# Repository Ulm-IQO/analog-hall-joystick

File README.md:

# Adjustable, Analog Hall Joystick

This joystick was designed to replace the failing resisitve joystick of a 
PI Micos SMC Corvus eco three-axis stepper motor controller.

The design has a primary XYZ joystick (Apem HF46S10) where the Z axis is 
the rotatable shaft and a secondary stick (Apem BF150A01BK0500) only 
for the Z axis.

Which Z axis is applied at the analog output can be controlled with a switch
while all four signals are available at the analog inputs of the integrated
Teensy 3.x microcontroller board.

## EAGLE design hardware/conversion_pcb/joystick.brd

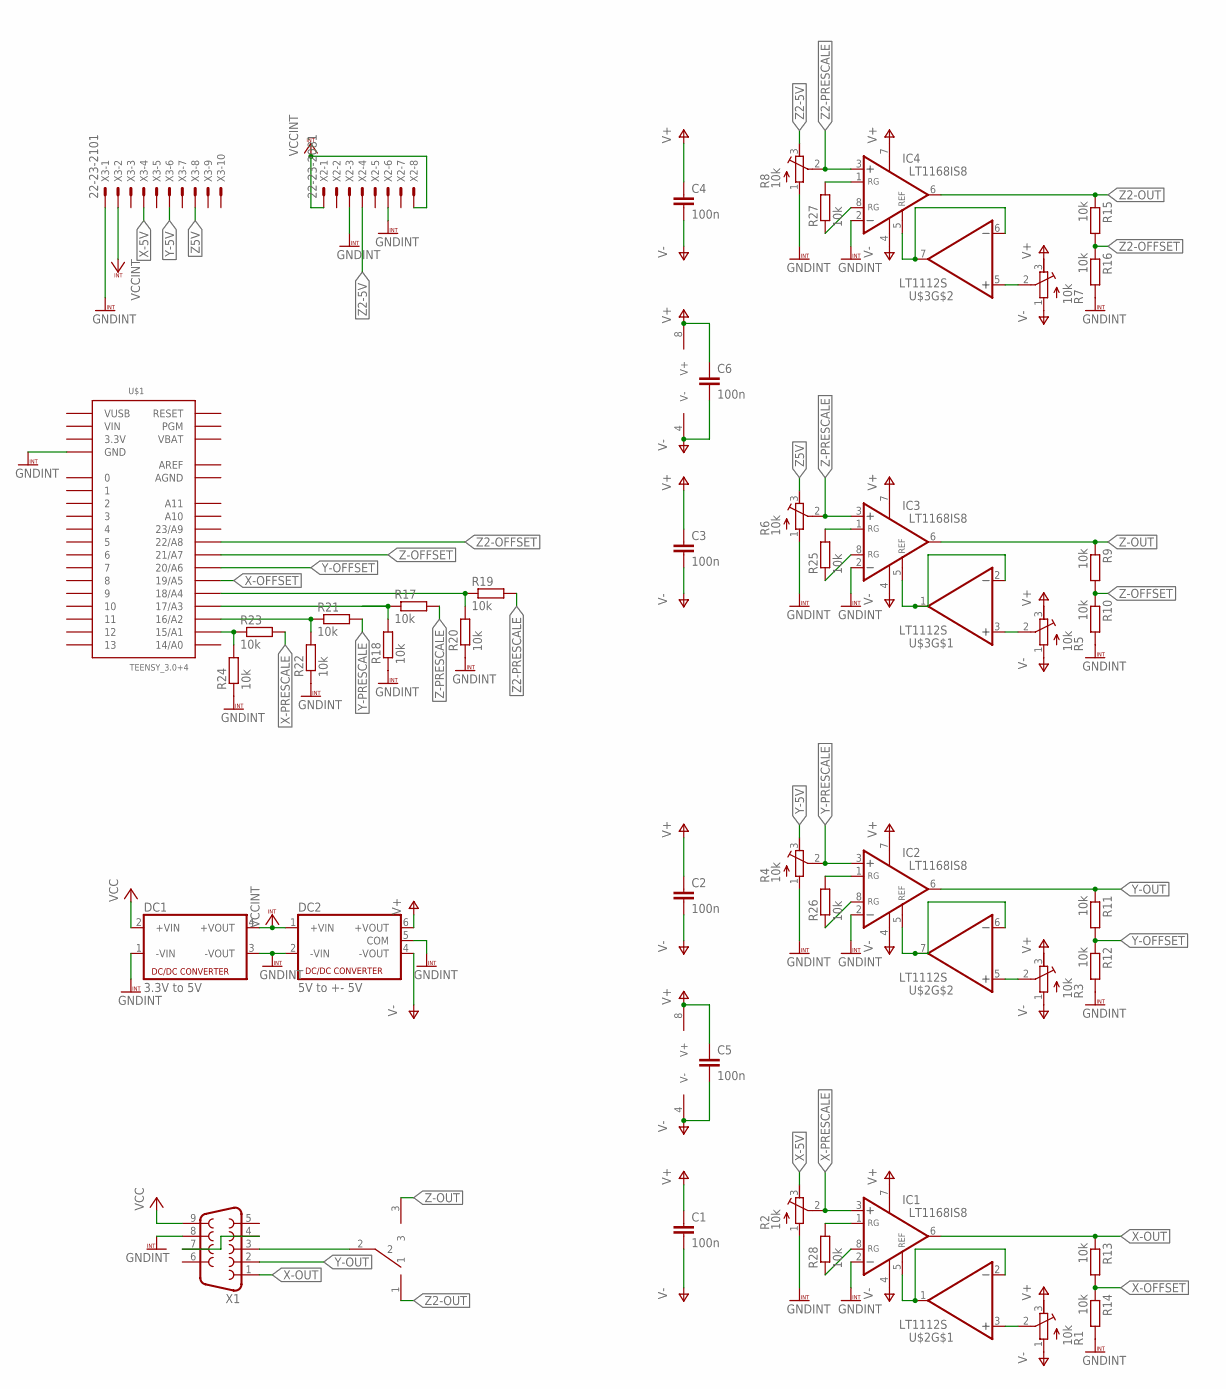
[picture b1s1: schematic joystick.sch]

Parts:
C1, C2, C3, C4, C5, C6: 100n; C1206
DC1: 3.3V to 5V; NME
DC2: 5V to +- 5V; NMA
IC1, IC2, IC3, IC4: LT1168IS8; SOIC8
R1, R2, R3, R4, R5, R6, R7, R8: 10k; RTRIM64W
R9, R10, R11, R12, R13, R14, R15, R16, R17, R18, R19, R20, R21, R22, R23, R24, R25, R26, R27, R28: 10k; R1206
U$1: TEENSY_3.0+4
U$2, U$3: LT1112S; SOIC8
U$4: MS12ASG40
X1: F09HP
X2: 22-23-2081
X3: 22-23-2101

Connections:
3.3V: U$1.3.3V, U$1.3.3V1 (3.3V)
AGND: U$1.AGND
AREF: U$1.AREF
GNDINT: DC1.1 (-VIN), DC1.3 (-VOUT), DC2.2 (-VIN), DC2.5 (COM), IC1.2 (-IN), IC2.2 (-IN), IC3.2 (-IN), IC4.2 (-IN), R2.1 (A), R4.1 (A), R6.1 (A), R8.1 (A), R10.2, R12.2, R14.2, R16.2, R18.1, R20.1, R22.1, R24.1, U$1.GND, U$1.GND1 (GND), X1.8, X2.3, X2.6, X3.1
unnamed: R1.2 (S), U$2.3 (+IN)
unnamed: R3.2 (S), U$2.5 (+IN)
unnamed: R5.2 (S), U$3.3 (+IN)
unnamed: R7.2 (S), U$3.5 (+IN)
unnamed: IC1.5 (REF), U$2.1 (OUT), U$2.2 (-IN)
unnamed: IC2.5 (REF), U$2.6 (-IN), U$2.7 (OUT)
unnamed: IC3.5 (REF), U$3.1 (OUT), U$3.2 (-IN)
unnamed: IC4.5 (REF), U$3.6 (-IN), U$3.7 (OUT)
unnamed: X1.4, X1.7
unnamed: U$4.2, X1.3
unnamed: R17.1, R18.2, U$1.17/A3
unnamed: R19.1, R20.2, U$1.18/A4
unnamed: R21.1, R22.2, U$1.16/A2
unnamed: R23.1, R24.2, U$1.15/A1
unnamed: IC1.8 (RG), R28.1
unnamed: IC1.1 (RG), R28.2
unnamed: IC2.1 (RG), R26.2
unnamed: IC2.8 (RG), R26.1
unnamed: IC3.1 (RG), R25.2
unnamed: IC3.8 (RG), R25.1
unnamed: IC4.8 (RG), R27.1
unnamed: IC4.1 (RG), R27.2
V+: C1.1, C2.1, C3.1, C4.1, C5.1, C6.1, DC2.6 (+VOUT), IC1.7 (V+), IC2.7 (V+), IC3.7 (V+), IC4.7 (V+), R1.3 (E), R3.3 (E), R5.3 (E), R7.3 (E), U$2.8 (V+), U$3.8 (V+)
V-: C1.2, C2.2, C3.2, C4.2, C5.2, C6.2, DC2.4 (-VOUT), IC1.4 (V-), IC2.4 (V-), IC3.4 (V-), IC4.4 (V-), R1.1 (A), R3.1 (A), R5.1 (A), R7.1 (A), U$2.4 (V-), U$3.4 (V-)
VBAT: U$1.VBAT
VCC: DC1.2 (+VIN), X1.9
VCCINT: DC1.4 (+VOUT), DC2.1 (+VIN), X2.1, X2.8, X3.2
VIN: U$1.VIN
VUSB: U$1.VUSB
X-5V: R2.3 (E), X3.4
X-OFFSET: R13.2, R14.1, U$1.19/A5
X-OUT: IC1.6 (OUT), R13.1, X1.1
X-PRESCALE: IC1.3 (+IN), R2.2 (S), R23.2
Y-5V: R4.3 (E), X3.6
Y-OFFSET: R11.2, R12.1, U$1.20/A6
Y-OUT: IC2.6 (OUT), R11.1, X1.2
Y-PRESCALE: IC2.3 (+IN), R4.2 (S), R21.2
Z2-5V: R8.3 (E), X2.4
Z2-OFFSET: R15.2, R16.1, U$1.22/A8
Z2-OUT: IC4.6 (OUT), R15.1, U$4.1
Z2-PRESCALE: IC4.3 (+IN), R8.2 (S), R19.2
Z5V: R6.3 (E), X3.8
Z-OFFSET: R9.2, R10.1, U$1.21/A7
Z-OUT: IC3.6 (OUT), R9.1, U$4.3
Z-PRESCALE: IC3.3 (+IN), R6.2 (S), R17.2

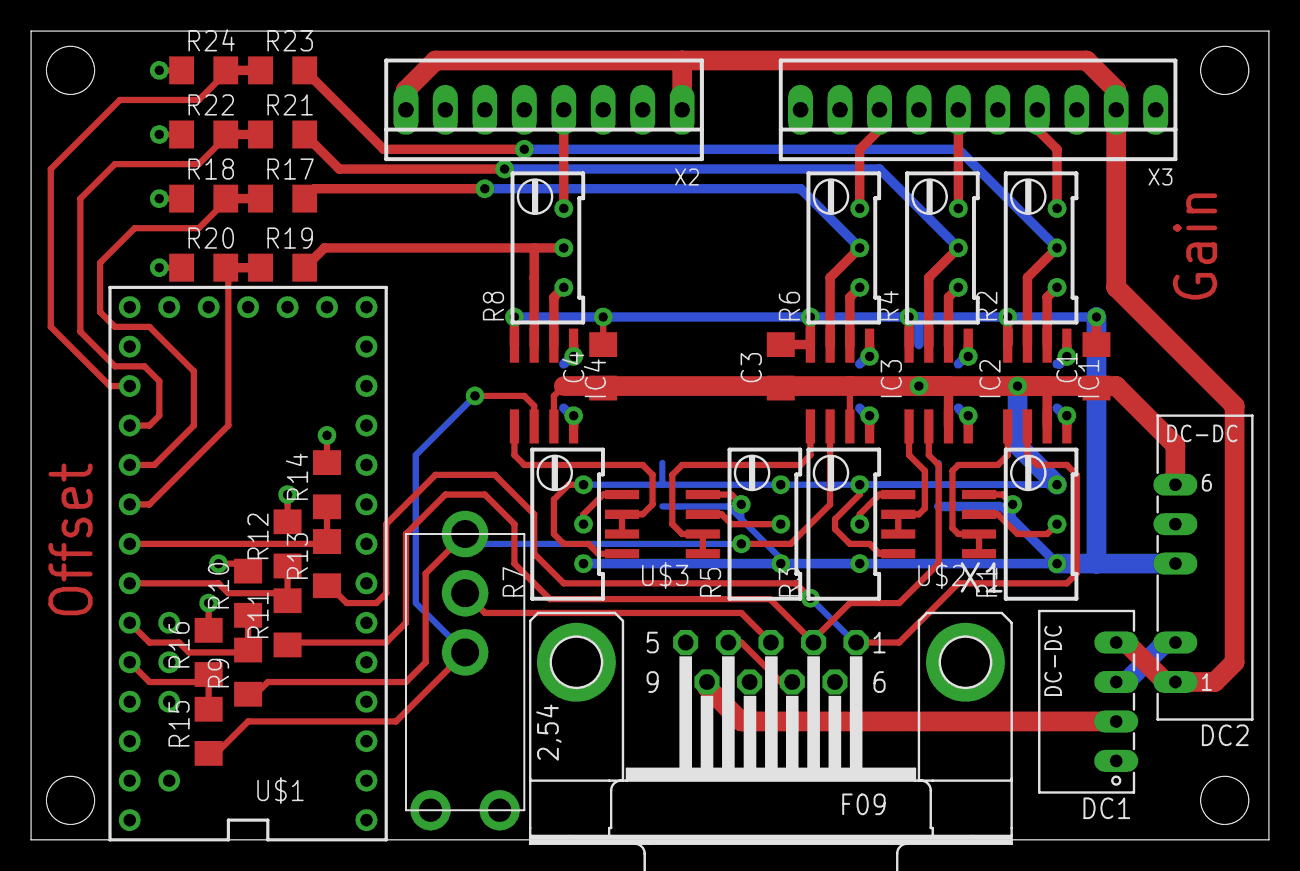
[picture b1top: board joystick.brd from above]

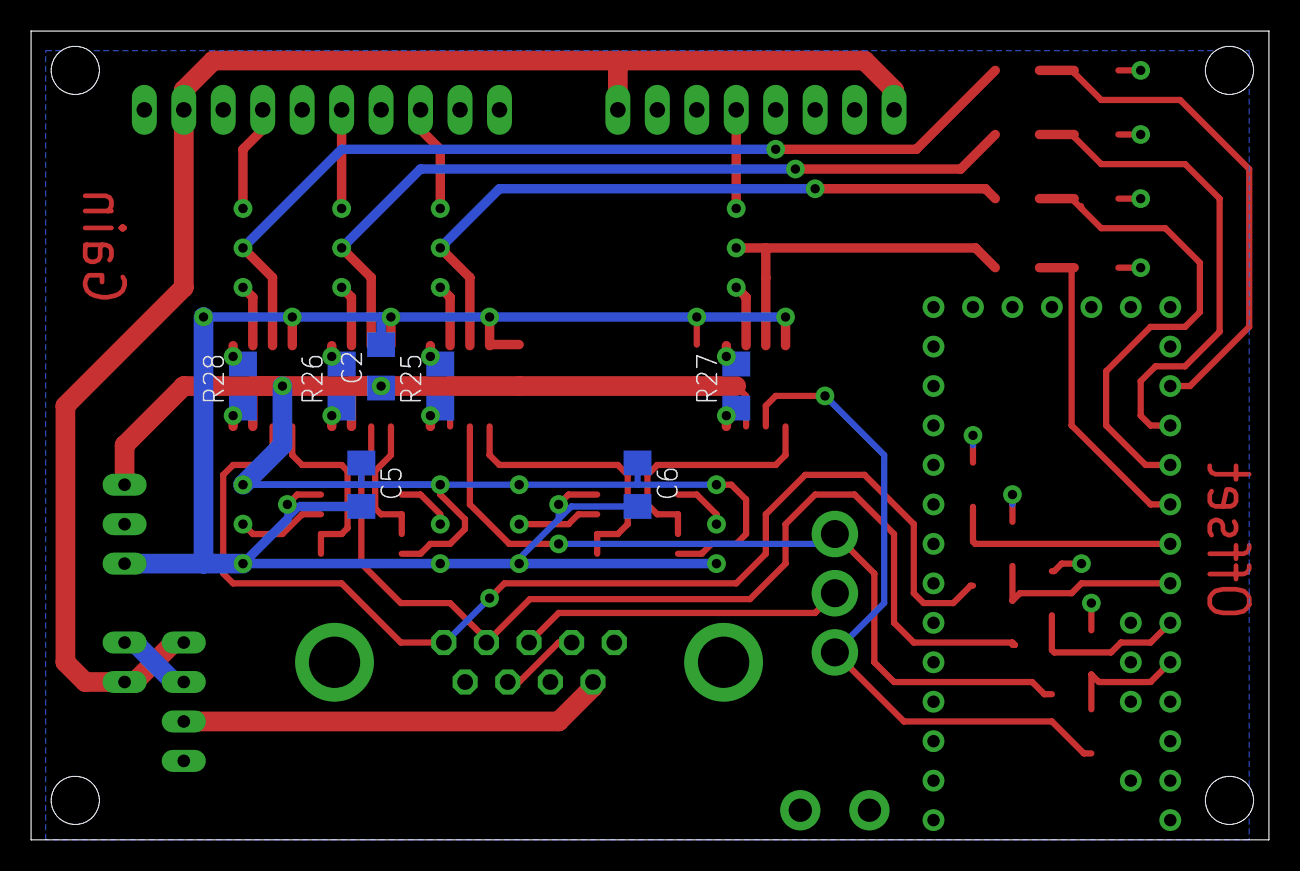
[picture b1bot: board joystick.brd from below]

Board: 2 copper layers, 79.7 x 52.1 mm, 47 parts (7 on the bottom side), 44 nets.

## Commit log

2016-05-28 hardware, test firmware and readmes
2016-07-06 declutter circuit schematic
2016-07-06 add license
